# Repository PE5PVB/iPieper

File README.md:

# iPieper: Uitgebreide 2m FM vossenjacht zender

De iPieper is een laagvermogen PLL gestuurde FM-vossenjachtzender met WAV/MP3 geheugen. Ook kun je
verschillende instellingen programmeren, zoals hoe lang de zender ingeschakeld of uitgeschakeld moet zijn, welk
bestand moet worden afgespeeld en op welke frequentie er moet worden uitgezonden. Je kunt elke willekeurige
frequentie tussen 144 en 146MHz gebruiken in een raster van 25kHz. Het is ook mogelijk om de iPieper zelf een
frequentie te laten kiezen wanneer deze begint met uitzenden.

Ook is er een header aanwezig met een aantal GPIOs. Zo kun je bijvoorbeeld zelf sensoren aansluiten. De software en
hardware is geheel opensource dus naar gelieve aan te passen.

Programmeren gaat via het Bluetooth serial protocol. Wanneer de iPieper met bijvoorbeeld een Windows laptop via
bluetooth is verbonden zal er een virtuele COM-poort beschikbaar komen om deze te programmeren.

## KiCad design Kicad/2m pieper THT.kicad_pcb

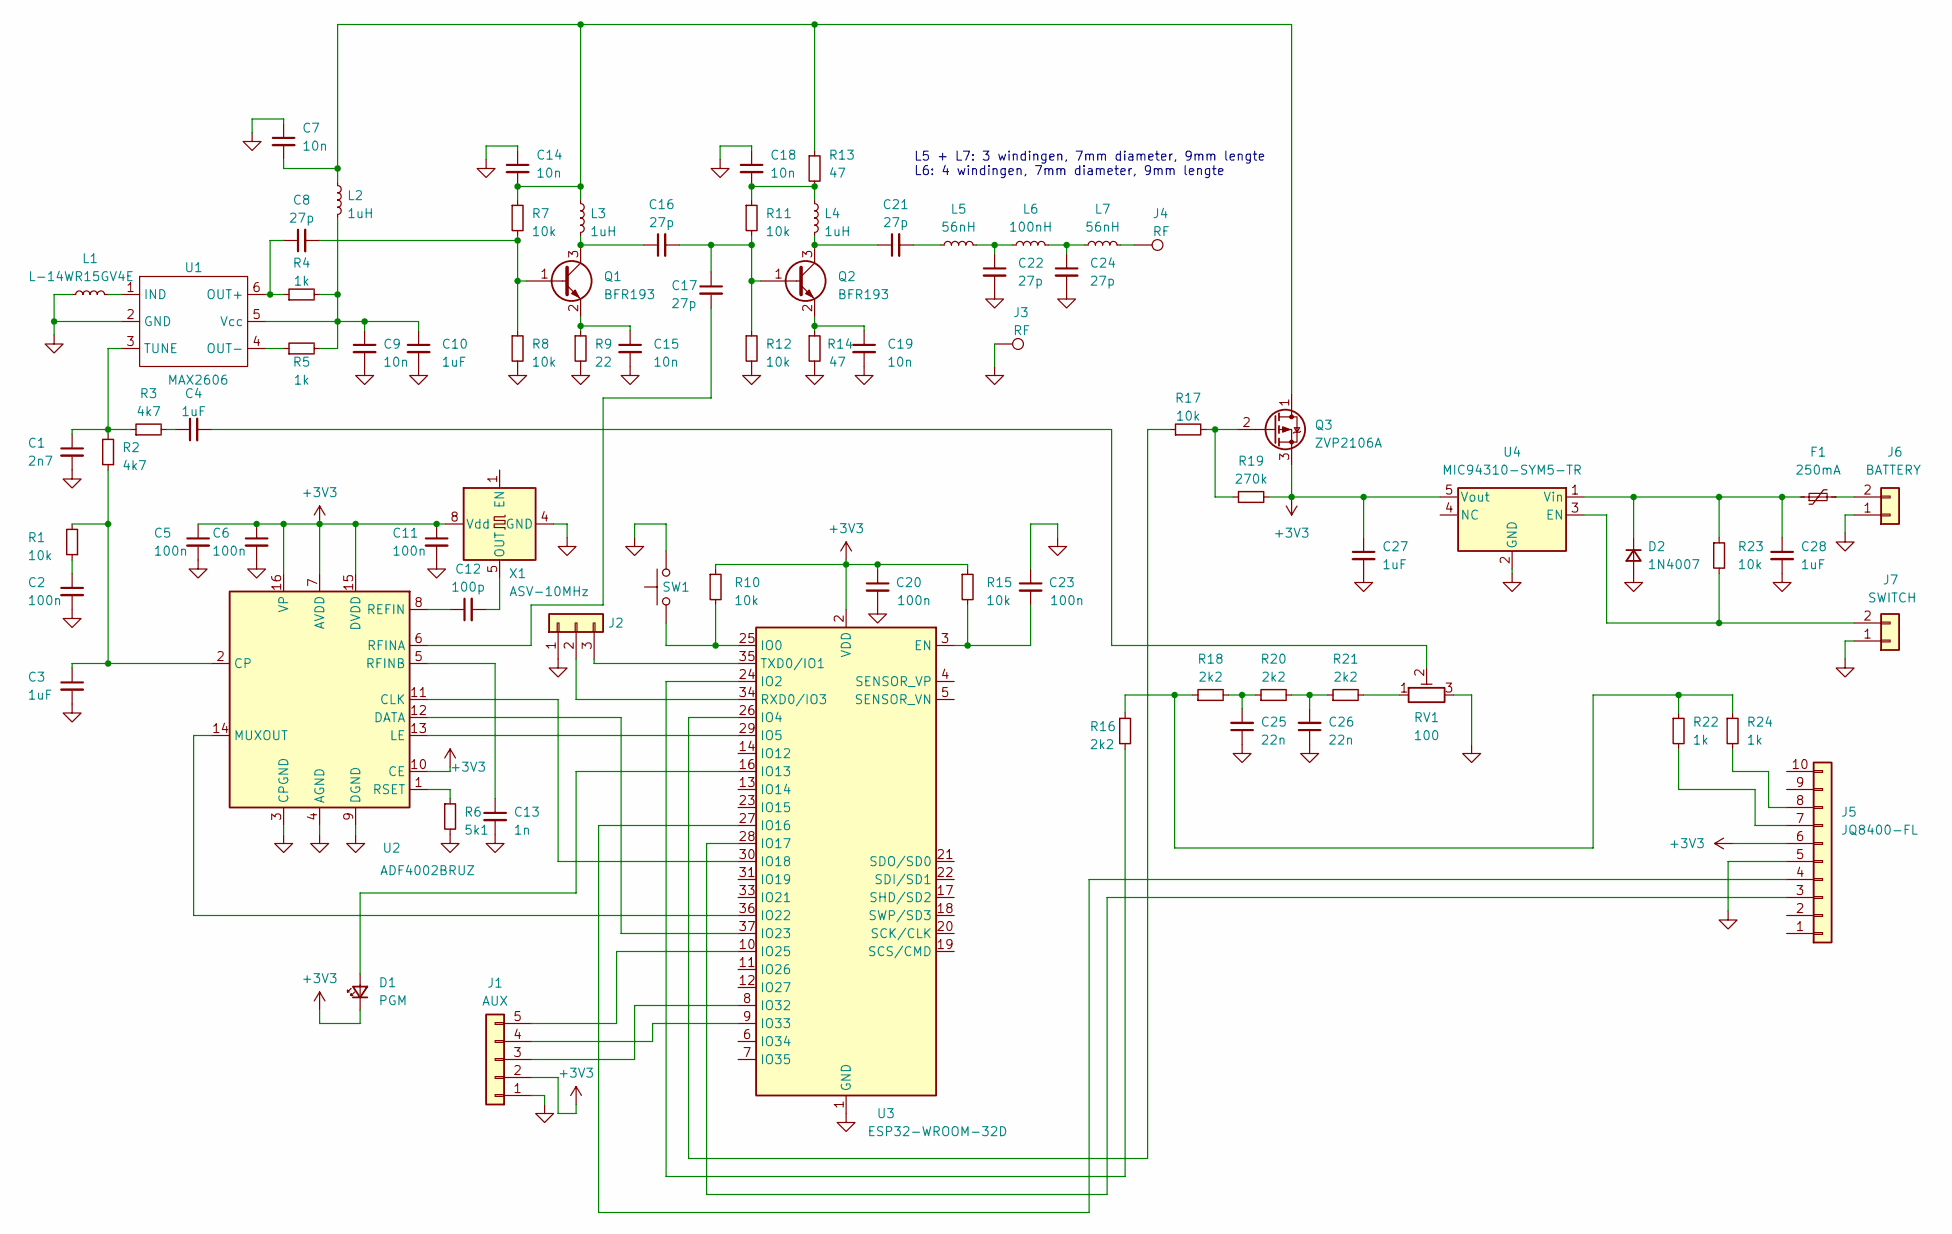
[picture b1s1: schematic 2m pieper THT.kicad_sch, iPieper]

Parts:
C1: 2n7; C_Disc_D3.0mm_W2.0mm_P2.50mm
C2, C5, C6, C11, C20, C23: 100n; C_Disc_D3.0mm_W2.0mm_P2.50mm
C3, C4, C10, C27, C28: 1uF; C_Disc_D3.0mm_W2.0mm_P2.50mm
C7, C9, C14, C15, C18, C19: 10n; C_Disc_D3.0mm_W2.0mm_P2.50mm
C8, C16, C17, C21, C22, C24: 27p; C_Disc_D3.0mm_W2.0mm_P2.50mm
C12: 100p; C_Disc_D3.0mm_W2.0mm_P2.50mm
C13: 1n; C_Disc_D3.0mm_W2.0mm_P2.50mm
C25, C26: 22n; C_Disc_D3.0mm_W2.0mm_P2.50mm
D1: PGM; LED_D3.0mm_FlatTop
D2: 1N4007; D_DO-41_SOD81_P10.16mm_Horizontal
F1: 250mA; C_Disc_D4.7mm_W2.5mm_P5.00mm
J1: AUX; PinHeader_1x05_P2.54mm_Vertical
J2: 1x3 header; PinHeader_1x03_P2.54mm_Vertical
J3, J4: RF; MountingHole_5.3mm_M5_Pad_Via
J5: JQ8400-FL; PinHeader_1x10_P2.54mm_Vertical
J6: BATTERY; PhoenixContact_MCV_1,5_2-G-3.81_1x02_P3.81mm_Vertical
J7: SWITCH; PhoenixContact_MCV_1,5_2-G-3.81_1x02_P3.81mm_Vertical
L1: L-14WR15GV4E; L_0603_1608Metric
L2, L3, L4: 1uH; R_Axial_DIN0207_L6.3mm_D2.5mm_P10.16mm_Horizontal
L5, L7: 56nH; L_Toroid_Horizontal_D6.5mm_P10.00mm_Diameter7-5mm_Amidon-T25
L6: 100nH; L_Toroid_Horizontal_D6.5mm_P10.00mm_Diameter7-5mm_Amidon-T25
Q1, Q2: BFR193; SOT-323_SC-70
Q3: ZVP2106A; TO-92Flat
R1, R7, R8, R10, R11, R12, R15, R17, R23: 10k; R_Axial_DIN0207_L6.3mm_D2.5mm_P10.16mm_Horizontal
R2, R3: 4k7; R_Axial_DIN0207_L6.3mm_D2.5mm_P10.16mm_Horizontal
R4, R5, R22, R24: 1k; R_Axial_DIN0207_L6.3mm_D2.5mm_P10.16mm_Horizontal
R6: 5k1; R_Axial_DIN0207_L6.3mm_D2.5mm_P10.16mm_Horizontal
R9: 22; R_Axial_DIN0207_L6.3mm_D2.5mm_P10.16mm_Horizontal
R13, R14: 47; R_Axial_DIN0207_L6.3mm_D2.5mm_P10.16mm_Horizontal
R16, R18, R20, R21: 2k2; R_Axial_DIN0207_L6.3mm_D2.5mm_P10.16mm_Horizontal
R19: 270k; R_Axial_DIN0207_L6.3mm_D2.5mm_P10.16mm_Horizontal
RV1: 100; Potentiometer_Vishay_T93YA_Vertical
SW1: SW_Push; SW_PUSH_6mm
U1: MAX2606; SOT-23-6
U2: ADF4002BRUZ; TSSOP-16_4.4x5mm_P0.65mm
U3: ESP32-WROOM-32D; ESP32-WROOM-32E
U4: MIC94310-SYM5-TR; SOT-23-5
X1: ASV-10MHz; Oscillator_DIP-8_LargePads

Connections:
+3V3: C5.1, C6.1, C11.1, C20.1, C27.1, D1.1 (K), J1.2, J5.6, Q3.3 (S), R10.1, R15.1, R19.2, U2.7 (AVDD), U2.10 (CE), U2.15 (DVDD), U2.16 (VP), U3.2 (VDD), U4.5 (Vout), X1.8 (Vdd)
GND: C1.2, C2.2, C3.2, C5.2, C6.2, C7.1, C9.2, C10.2, C11.2, C13.2, C14.1, C15.2, C18.1, C19.2, C20.2, C22.2, C23.1, C24.2, C25.1, C26.1, C27.2, C28.2, D2.2 (A), J1.1, J2.1, J3.1, J5.5, J6.1, J7.1, L1.1, R6.2, R8.2, R9.2, R12.2, R14.2, RV1.3, SW1.2, U1.2 (GND), U2.3 (CPGND), U2.4 (AGND), U2.9 (DGND), U3.1 (GND), U3.15 (GND), U3.38 (GND), U3.39 (GND), U4.2 (GND), X1.4 (GND)
unnamed: C2.1, R1.1
unnamed: C4.1, R3.2
unnamed: C4.2, RV1.2
unnamed: C18.2, L4.1, R11.1, R13.2
unnamed: C21.2, L5.1
unnamed: C22.1, L5.2, L6.1
unnamed: C24.1, L6.2, L7.1
unnamed: C25.2, R18.2, R20.1
unnamed: C26.2, R20.2, R21.1
unnamed: D1.2 (A), U3.16 (IO13)
unnamed: C28.1, D2.1 (K), F1.1, R23.1, U4.1 (Vin)
unnamed: J1.3, U3.8 (IO32)
unnamed: J1.4, U3.9 (IO33)
unnamed: J1.5, U3.10 (IO25)
unnamed: J2.2, U3.34 (RXD0/IO3)
unnamed: J2.3, U3.35 (TXD0/IO1)
unnamed: J4.1, L7.2
unnamed: J5.3, U3.28 (IO17)
unnamed: J5.4, U3.27 (IO16)
unnamed: J5.7, R22.2
unnamed: J5.8, R24.2
unnamed: F1.2, J6.2
unnamed: J7.2, R23.2, U4.3 (EN)
unnamed: C8.2, Q1.1 (B), R7.2, R8.1
unnamed: C16.1, L3.2, Q1.3 (C)
unnamed: C15.1, Q1.2 (E), R9.1
unnamed: C16.2, C17.1, Q2.1 (B), R11.2, R12.1
unnamed: C21.1, L4.2, Q2.3 (C)
unnamed: C19.1, Q2.2 (E), R14.1
unnamed: C7.2, C14.2, L2.1, L3.1, Q3.1 (D), R7.1, R13.1
unnamed: Q3.2 (G), R17.2, R19.1
unnamed: R16.1, R18.1, R22.1, R24.1
unnamed: R21.2, RV1.1
unnamed: L1.2, U1.1 (IND)
unnamed: C8.1, R4.1, U1.6 (OUT+)
unnamed: R5.1, U1.4 (OUT-)
unnamed: C1.1, R2.2, R3.1, U1.3 (TUNE)
unnamed: C9.1, C10.1, L2.2, R4.2, R5.2, U1.5 (Vcc)
unnamed: U2.11 (CLK), U3.30 (IO18)
unnamed: C3.1, R1.2, R2.1, U2.2 (CP)
unnamed: U2.12 (DATA), U3.37 (IO23)
unnamed: U2.13 (LE), U3.29 (IO5)
unnamed: U2.14 (MUXOUT), U3.36 (IO22)
unnamed: C12.1, U2.8 (REFIN)
unnamed: C17.2, U2.6 (RFINA)
unnamed: C13.1, U2.5 (RFINB)
unnamed: R6.1, U2.1 (RSET)
unnamed: C23.2, R15.2, U3.3 (EN)
unnamed: R10.2, SW1.1, U3.25 (IO0)
unnamed: R16.2, U3.24 (IO2)
unnamed: R17.1, U3.26 (IO4)
unnamed: C12.2, X1.5 (OUT)

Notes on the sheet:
L5 + L7: 3 windingen, 7mm diameter, 9mm lengte L6: 4 windingen, 7mm diameter, 9mm lengte

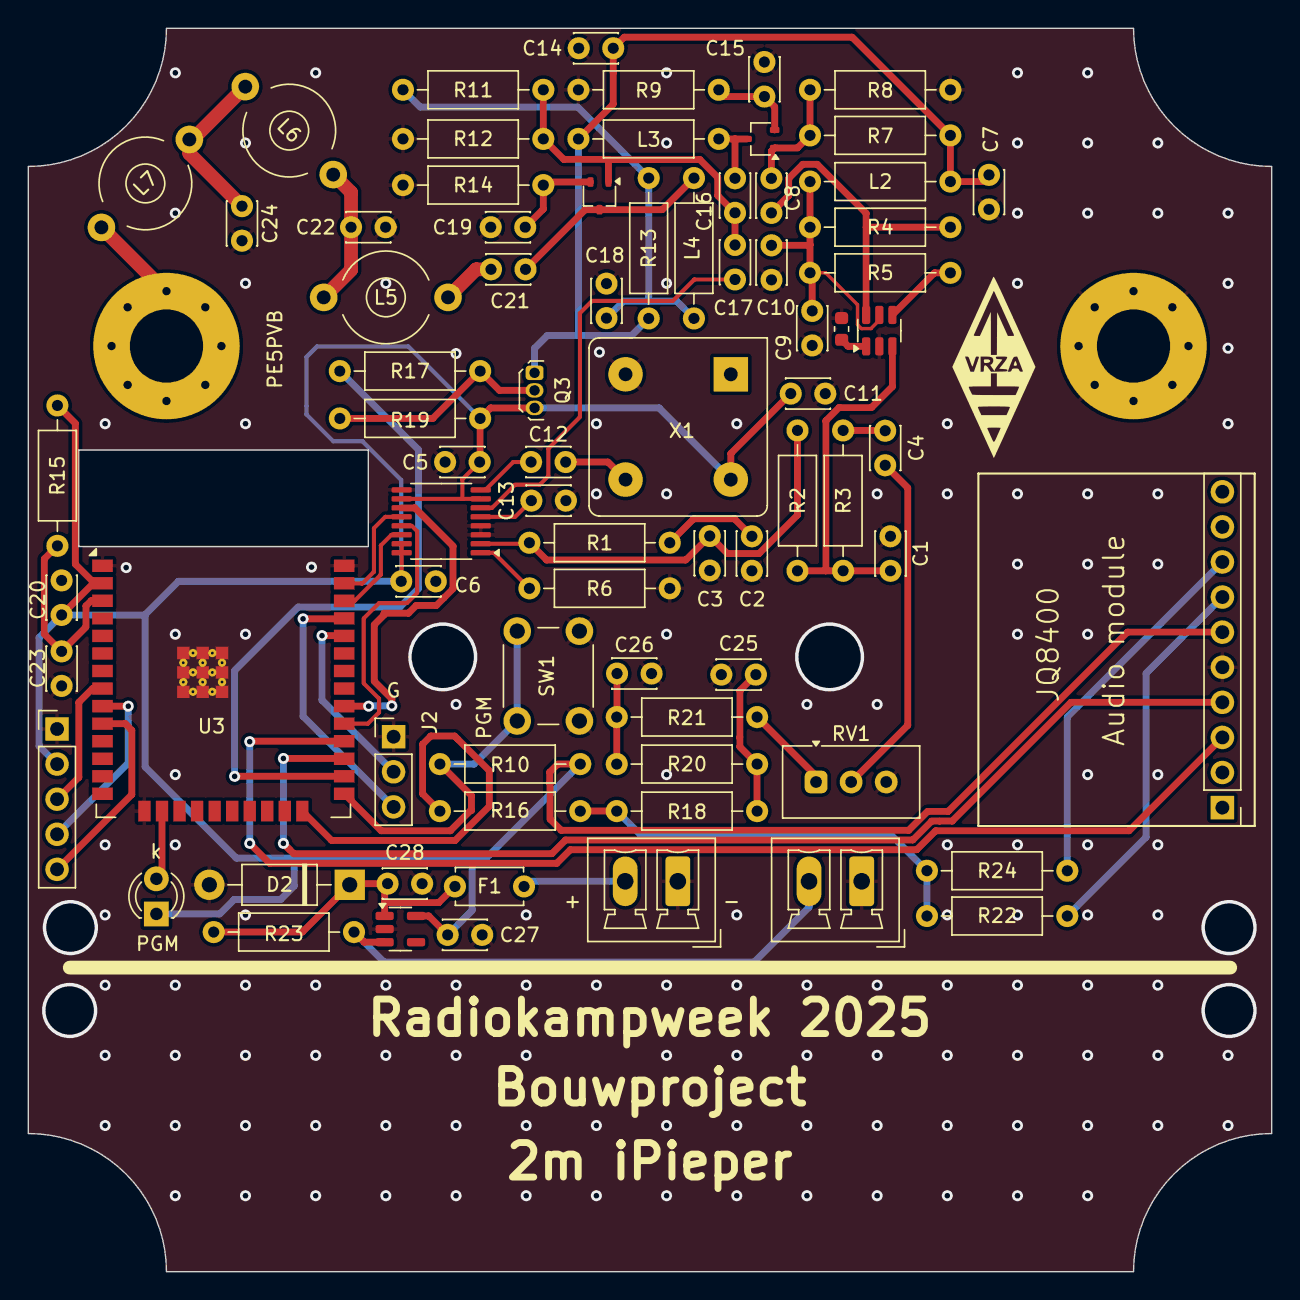
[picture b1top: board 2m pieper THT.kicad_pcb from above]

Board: 2 copper layers, 90.0 x 90.0 mm, 79 parts (0 on the bottom side), 54 nets.

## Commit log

2025-04-22 Upload Kicad files
2025-04-22 Upload software
2025-04-22 Added files
2025-04-25 Update data
2025-05-06 Adjusting tabs
2025-06-12 Modificaties
2026-05-29 VB Code compatibility, code update
